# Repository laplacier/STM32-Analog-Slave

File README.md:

https://www.laplacier.com/stm32-analog-slave

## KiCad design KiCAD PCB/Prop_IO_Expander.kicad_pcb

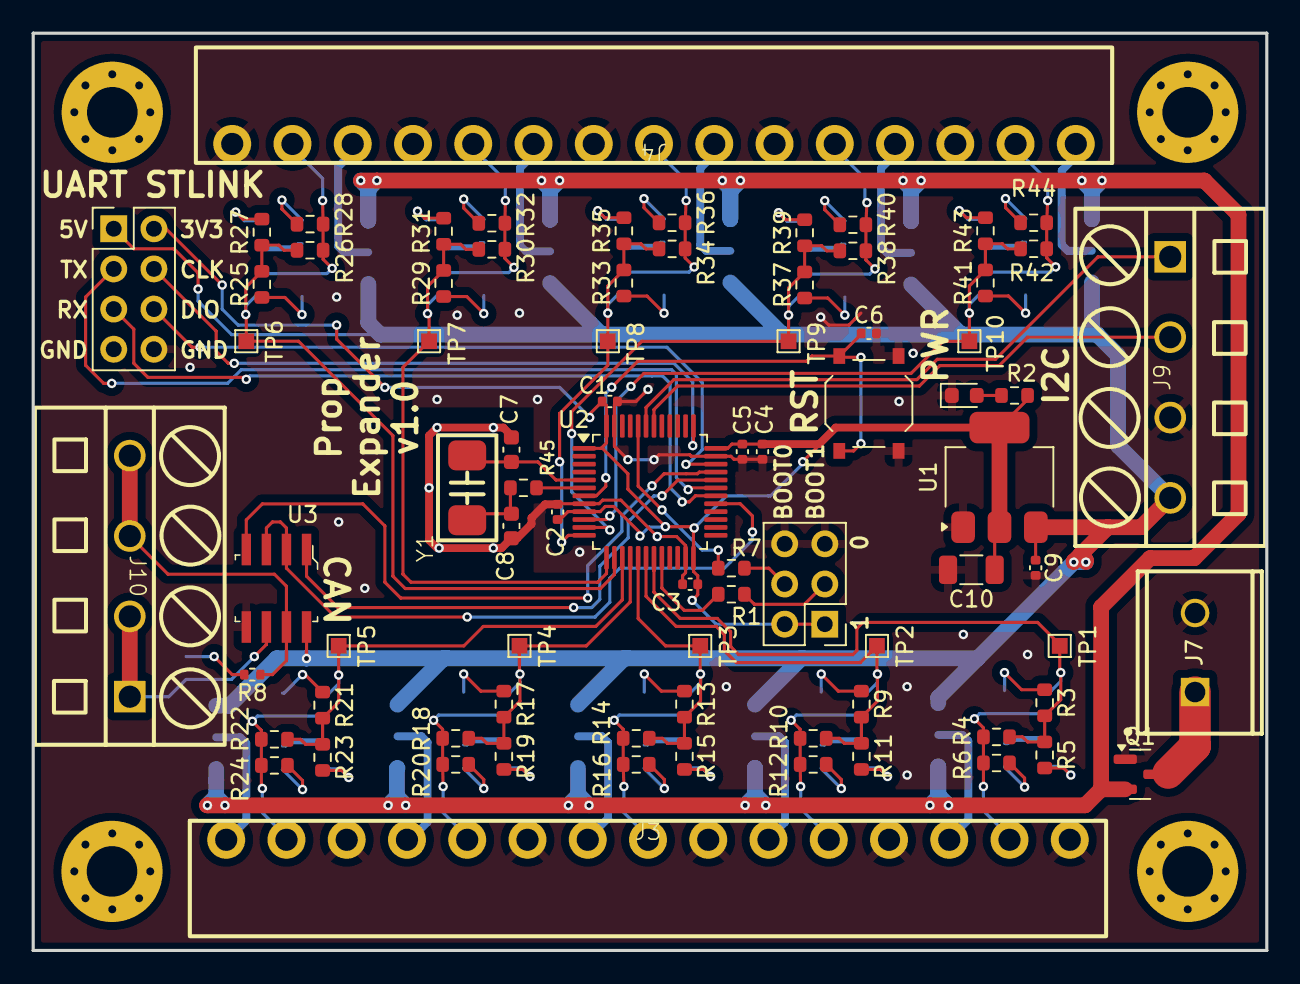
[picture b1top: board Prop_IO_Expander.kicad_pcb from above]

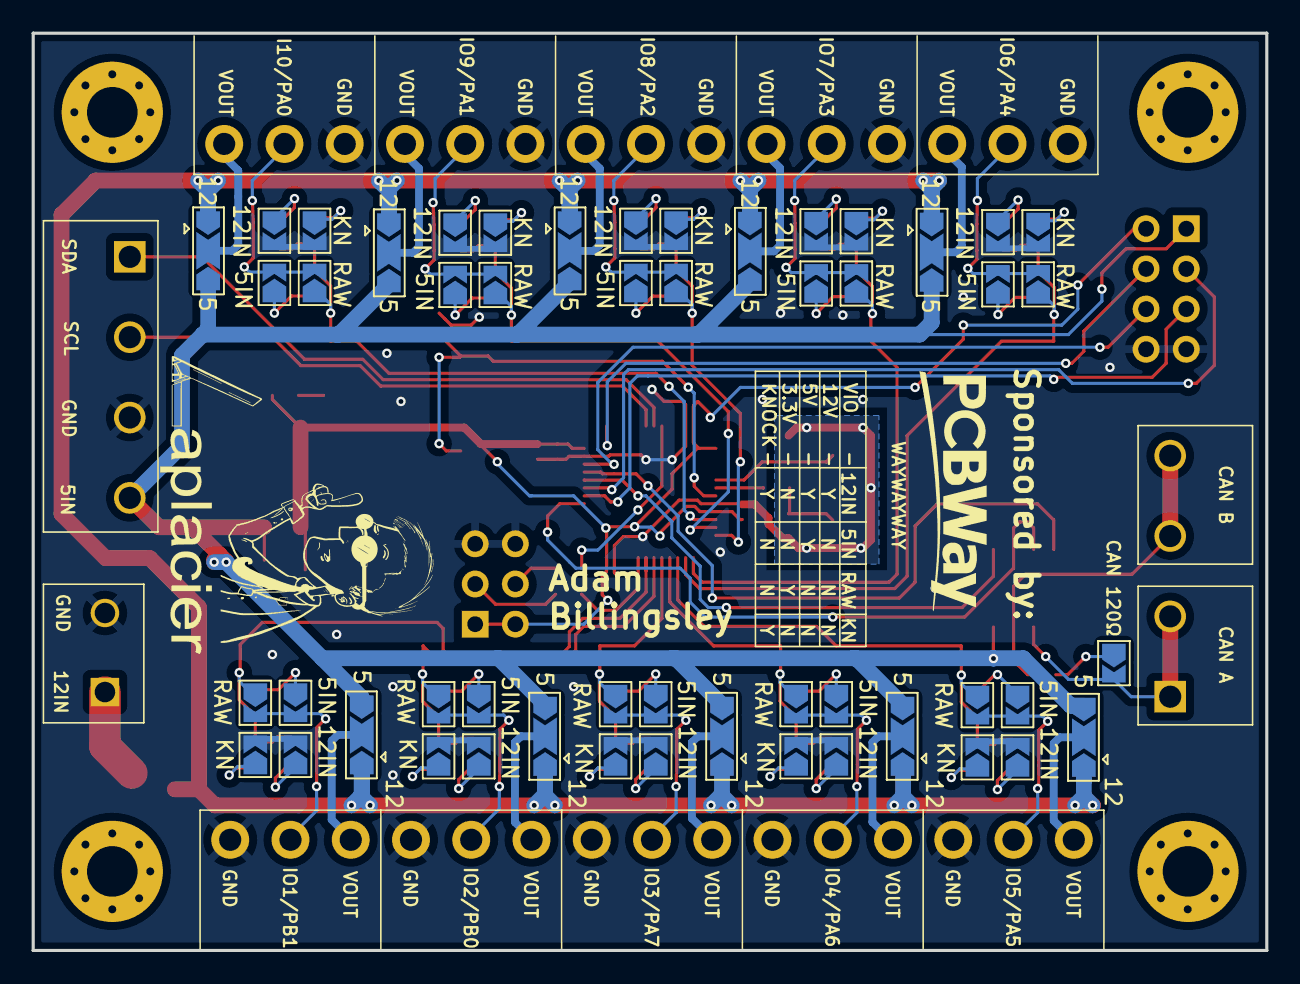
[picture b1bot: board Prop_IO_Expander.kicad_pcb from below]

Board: 2 copper layers, 78.0 x 58.0 mm, 130 parts (51 on the bottom side), 86 nets.

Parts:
C1, C2, C3, C4, C9: 1uF; C_0402_1005Metric
C5, C6: 10nF; C_0402_1005Metric
C7, C8: 30pF; C_0603_1608Metric
C10: 22uF; C_1206_3216Metric
D1: LED; LED_0603_1608Metric
J2: BOOT; PinHeader_2x03_P2.54mm_Vertical
J3, J4: Conn_01x15_Socket; MAX_MX15EDGRC_15P_P3.81_Horizontal
J7: XY301V-A-5.0-2P; TerminalBlock_Wuerth_691137710002_P5.0mm
J8: Conn_02x05_Odd_Even; PinHeader_2x04_P2.54mm_Vertical
J9, J10: Screw_Terminal_01x04; TerminalBlock_Dorabo-4_P5.08mm
JP1, JP6, JP11, JP16, JP21, JP26, JP31, JP36, JP41, JP46: Jumper_3_Open; SolderJumper-3_P2.0mm_Open_TrianglePad1.0x1.5mm
JP2, JP3, JP4, JP5, JP7, JP8, JP9, JP10, JP12, JP13, JP14, JP15, JP17, JP18, JP19, JP20, JP22, JP23, JP24, JP25, JP27, JP28, JP29, JP30, JP32, JP33, JP34, JP35, JP37, JP38, JP39, JP40, JP42, JP43, JP44, JP45, JP47, JP48, JP49, JP50, JP51: Jumper_2_Open; SolderJumper-2_P1.3mm_Open_TrianglePad1.0x1.5mm
Q1: AO3401A; SOT-23
R1, R2, R7: 10k; R_0603_1608Metric
R3, R9, R13, R17, R21, R25, R29, R33, R37, R41: 6.8kΩ; R_0603_1608Metric
R4, R10, R14, R18, R22, R26, R30, R34, R38, R42: 27kΩ; R_0603_1608Metric
R5, R11, R15, R19, R23, R27, R31, R35, R39, R43: 10kΩ; R_0603_1608Metric
R6, R12, R16, R20, R24, R28, R32, R36, R40, R44: 1MΩ; R_0603_1608Metric
R8: 120Ω; R_0402_1005Metric
R45: 680Ω; R_0603_1608Metric
SW1: RESET; SW_Push_1P1T_XKB_TS-1187A
TP1, TP2, TP3, TP4, TP5, TP6, TP7, TP8, TP9, TP10: TestPoint; TestPoint_Pad_1.0x1.0mm
U1: AMS1117-3.3; SOT-223-3_TabPin2
U2: STM32F103C8T6; LQFP-48_7x7mm_P0.5mm
U3: SP3485EN-L_TR; SOIC-8_W3.9mm
Y1: 8MHz; CRYSTAL-SMD_L5.0-W3.2

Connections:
+3.3V: C1.1, C2.1, C3.1, C4.1, C5.1, C10.1, J2.1, J2.2, J8.2, R2.1, U1.2 (VO), U2.1 (VBAT), U2.9 (VDDA), U2.24 (VDD), U2.36 (VDD), U2.48 (VDD)
+5V: C9.1, J8.1, J9.4, JP1.3 (B), JP6.3 (B), JP11.3 (B), JP16.3 (B), JP21.3 (B), JP26.3 (B), JP31.3 (B), JP36.3 (B), JP41.3 (B), JP46.3 (B), U1.3 (VI), U3.8 (VCC)
+12V: JP1.1 (A), JP6.1 (A), JP11.1 (A), JP16.1 (A), JP21.1 (A), JP26.1 (A), JP31.1 (A), JP36.1 (A), JP41.1 (A), JP46.1 (A), Q1.2 (S)
/BOOT0: R7.2, U2.44 (BOOT0)
/BOOT1: R1.1, U2.20 (PB2)
/CAN_EN: U2.29 (PA8), U3.2 (~RE), U3.3 (DE)
/CAN_RX: U2.32 (PA11), U3.1 (RO)
/CAN_TX: U2.33 (PA12), U3.4 (DI)
/I2C_SCL: J9.2, U2.42 (PB6)
/I2C_SDA: J9.1, U2.43 (PB7)
/Input1/INPUT: J3.2, JP2.2 (B), JP3.2 (B), R4.2, R6.1
/Input1/VCC: J3.3, JP1.2 (C)
/Input2/INPUT: J3.5, JP7.2 (B), JP8.2 (B), R10.2, R12.1
/Input2/VCC: J3.6, JP6.2 (C)
/Input3/INPUT: J3.8, JP12.2 (B), JP13.2 (B), R14.2, R16.1
/Input3/VCC: J3.9, JP11.2 (C)
/Input4/INPUT: J3.11, JP17.2 (B), JP18.2 (B), R18.2, R20.1
/Input4/VCC: J3.12, JP16.2 (C)
/Input5/INPUT: J3.14, JP22.2 (B), JP23.2 (B), R22.2, R24.1
/Input5/VCC: J3.15, JP21.2 (C)
/Input6/INPUT: J4.2, JP27.2 (B), JP28.2 (B), R26.2, R28.1
/Input6/VCC: J4.3, JP26.2 (C)
/Input7/INPUT: J4.5, JP32.2 (B), JP33.2 (B), R30.2, R32.1
/Input7/VCC: J4.6, JP31.2 (C)
/Input8/INPUT: J4.8, JP37.2 (B), JP38.2 (B), R34.2, R36.1
/Input8/VCC: J4.9, JP36.2 (C)
/Input9/INPUT: J4.11, JP42.2 (B), JP43.2 (B), R38.2, R40.1
/Input9/VCC: J4.12, JP41.2 (C)
/Input10/INPUT: J4.14, JP47.2 (B), JP48.2 (B), R42.2, R44.1
/Input10/VCC: J4.15, JP46.2 (C)
/NRST: C6.1, SW1.1, U2.7 (NRST)
/PA0: JP48.1 (A), R41.1, R42.1, R43.1, TP10.1, U2.10 (PA0)
/PA1: JP43.1 (A), R37.1, R38.1, R39.1, TP9.1, U2.11 (PA1)
/PA2: JP38.1 (A), R33.1, R34.1, R35.1, TP8.1, U2.12 (PA2)
/PA3: JP33.1 (A), R29.1, R30.1, R31.1, TP7.1, U2.13 (PA3)
/PA4: JP28.1 (A), R25.1, R26.1, R27.1, TP6.1, U2.14 (PA4)
/PA5: JP23.1 (A), R21.1, R22.1, R23.1, TP5.1, U2.15 (PA5)
/PA6: JP18.1 (A), R17.1, R18.1, R19.1, TP4.1, U2.16 (PA6)
/PA7: JP13.1 (A), R13.1, R14.1, R15.1, TP3.1, U2.17 (PA7)
/PB0: JP8.1 (A), R9.1, R10.1, R11.1, TP2.1, U2.18 (PB0)
/PB1: JP3.1 (A), R3.1, R4.1, R5.1, TP1.1, U2.19 (PB1)
/PD0: C7.2, U2.5 (PD0), Y1.2
/PD1: R45.1, U2.6 (PD1)
/SWCLK: J8.4, U2.37 (PA14)
/SWDIO: J8.6, U2.34 (PA13)
/UART_RX0: J8.5, U2.30 (PA9)
/UART_TX0: J8.3, U2.31 (PA10)
GND: C1.2, C2.2, C3.2, C4.2, C5.2, C6.2, C7.1, C8.1, C9.2, C10.2, D1.1 (K), J2.5, J2.6, J3.1, J3.4, J3.7, J3.10, J3.13, J4.1, J4.4, J4.7, J4.10, J4.13, J7.2, J8.7, J8.8, J9.3, JP4.2 (B), JP5.2 (B), JP9.2 (B), JP10.2 (B), JP14.2 (B), JP15.2 (B), JP19.2 (B), JP20.2 (B), JP24.2 (B), JP25.2 (B), JP29.2 (B), JP30.2 (B), JP34.2 (B), JP35.2 (B), JP39.2 (B), JP40.2 (B), JP44.2 (B), JP45.2 (B), JP49.2 (B), JP50.2 (B), Q1.1 (G), SW1.2, U1.1 (GND), U2.8 (VSSA), U2.23 (VSS), U2.35 (VSS), U2.47 (VSS), U3.5 (GND)
unnamed: C8.2, R45.2, Y1.1
unnamed: D1.2 (A), R2.2
unnamed: J2.3, R1.2
unnamed: J2.4, R7.1
unnamed: J10.1, J10.2, JP51.2 (B), U3.6 (A)
unnamed: J10.3, J10.4, R8.2, U3.7 (B)
unnamed: JP2.1 (A), R3.2
unnamed: JP4.1 (A), R6.2
unnamed: JP5.1 (A), R5.2
unnamed: JP7.1 (A), R9.2
unnamed: JP9.1 (A), R12.2
unnamed: JP10.1 (A), R11.2
unnamed: JP12.1 (A), R13.2
unnamed: JP14.1 (A), R16.2
unnamed: JP15.1 (A), R15.2
unnamed: JP17.1 (A), R17.2
unnamed: JP19.1 (A), R20.2
unnamed: JP20.1 (A), R19.2
unnamed: JP22.1 (A), R21.2
unnamed: JP24.1 (A), R24.2
unnamed: JP25.1 (A), R23.2
unnamed: JP27.1 (A), R25.2
unnamed: JP29.1 (A), R28.2
unnamed: JP30.1 (A), R27.2
unnamed: JP32.1 (A), R29.2
unnamed: JP34.1 (A), R32.2
unnamed: JP35.1 (A), R31.2
unnamed: JP37.1 (A), R33.2
unnamed: JP39.1 (A), R36.2
unnamed: JP40.1 (A), R35.2
unnamed: JP42.1 (A), R37.2
unnamed: JP44.1 (A), R40.2
unnamed: JP45.1 (A), R39.2
unnamed: JP47.1 (A), R41.2
unnamed: JP49.1 (A), R44.2
unnamed: JP50.1 (A), R43.2
unnamed: JP51.1 (A), R8.1
VDC: J7.1, Q1.3 (D)

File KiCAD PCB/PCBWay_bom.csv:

Item #,*Designator,*Qty,Manufacturer,*Mfg Part #,Description / Value,*Package/Footprint ,Type,Your Instructions / Notes
1,"C1,C2,C3,C4,C9",5,Samsung Electro-Mechanics,CL05A105KA5NQNC ,25V 1uF X5R ±10% 0402 Multilayer Ceramic Capacitors MLCC - SMD/SMT ROHS ,0402,SMD,
2,"C5,C6",2,Samsung Electro-Mechanics,CL05B103KB5NNNC ,50V 10nF X7R ±10% 0402 Multilayer Ceramic Capacitors MLCC - SMD/SMT ROHS ,0402,SMD,
3,"C7,C8",2,FH (Guangdong Fenghua Advanced Tech) ,0603CG300J500NT ,50V 30pF C0G ±5% 0603 Multilayer Ceramic Capacitors MLCC - SMD/SMT ROHS ,0603,SMD,
4,C10,1,Samsung Electro-Mechanics,CL31A226KAHNNNE ,25V 22uF X5R ±10% 1206 Multilayer Ceramic Capacitors MLCC - SMD/SMT ROHS ,1206,SMD,
5,D1,1,Hubei KENTO Elec ,KT-0603R ,-40℃~+85℃ Red 0603 Light Emitting Diodes (LED) ROHS ,0603,SMD,
6,J2,1,,,Pin Header_2x03_P2.54mm_Vertical,SMT-2x03P,thru-hole,
7,"J3,J4",2,MAX,MX15EDGRC-3.81-15P-GN01-Cu-A ,"300V 8A 15 Bend -40℃~+105℃ Copper Alloy 1 3.81mm 1x15P Green Board Edge/Receptacle-Close Tin Push-Pull,P=3.81mm Pluggable System Terminal Block ROHS ",SMT-15P,thru-hole,
8,J8,1,,Conn_02x05_Odd_Even,Pin Header_2x04_P2.54mm_Vertical,SMT-2x04P,thru-hole,
9,"J9,J10",2,DORABO,DB127S-5.08-4P-GN ,P=5.08mm Screw terminal ROHS ,SMT-4P,thru-hole,
10,Q1,1,Alpha & Omega Semicon,AO3401A,"30V 4A 44mΩ@10V,4.3A 1.4W 1.3V@250uA 1PCSPChannel SOT-23 MOSFETs ROHS ",23-SOT,SMD,
11,"R1,R2,R7",3,UNI-ROYAL(厚声),0603WAF1002T5E,100mW Thick Film Resistors 75V ±100ppm/℃ ±1% 10kΩ 0603 Chip Resistor - Surface Mount ROHS ,0603,SMD,
12,"R3,R9,R13,R17,R21,R25,R29,R33,R37,R41",10,UNI-ROYAL(厚声),0603WAF6801T5E ,100mW Thick Film Resistors 75V ±100ppm/℃ ±1% 6.8kΩ 0603 Chip Resistor - Surface Mount ROHS ,0603,SMD,
13,"R4,R10,R14,R18,R22,R26,R30,R34,R38,R42",10,UNI-ROYAL(厚声),0603WAF2702T5E ,100mW Thick Film Resistors 75V ±100ppm/℃ ±1% 27kΩ 0603 Chip Resistor - Surface Mount ROHS ,0603,SMD,
14,"R5,R11,R15,R19,R23,R27,R31,R35,R39,R43",10,UNI-ROYAL(厚声),0603WAF1002T5E ,100mW Thick Film Resistors 75V ±100ppm/℃ ±1% 10kΩ 0603 Chip Resistor - Surface Mount ROHS ,0603,SMD,
15,"R6,R12,R16,R20,R24,R28,R32,R36,R40,R44",10,UNI-ROYAL(厚声),0603WAF1004T5E ,100mW Thick Film Resistors 75V ±100ppm/℃ ±1% 1MΩ 0603 Chip Resistor - Surface Mount ROHS ,0603,SMD,
16,R8,1,UNI-ROYAL(厚声),0402WGF1200TCE ,62.5mW Thick Film Resistors 50V ±100ppm/℃ ±1% 120Ω 0402 Chip Resistor - Surface Mount ROHS ,0402,SMD,
17,R45,1,UNI-ROYAL(厚声),0603WAF6800T5E ,100mW Thick Film Resistors 75V ±100ppm/℃ ±1% 680Ω 0603 Chip Resistor - Surface Mount ROHS ,0603,SMD,
18,SW1,1,XKB Connection ,TS-1187A-B-A-B ,"No Without 50mA 5.1mm 100,000 Times 160gf 12V 5.1mm 1.5mm Round Button Brick nogging SPST SMD Tactile Switches ROHS",SMD,SMD,
19,U1,1,Advanced Monolithic Systems ,AMS1117-3.3,72dB@(120Hz) 1A Fixed 3.3V Positive electrode SOT-223-3 Linear Voltage Regulators (LDO) ROHS ,223-3-SOT,SMD,
20,U2,1,STMicroelectronics,STM32F103C8T6,64KB 2V~3.6V ARM-M3 20KB 72MHz FLASH 37 LQFP-48(7x7) Microcontroller Units (MCUs/MPUs/SOCs) ROHS ,48-LQFP,SMD/LQFP,
21,U3,1,"MaxLinear, Inc.",SP3485EN-L_TR,transceiver 10Mbps 1/1 SOIC-8 RS-485/RS-422 ICs ROHS ,8-SOIC,SMD,
22,Y1,1,YXC ,X50328MSB2GI ,8MHz Surface mount crystal oscillator 20pF ±10ppm ±20ppm SMD5032 Crystals ROHS ,SMD,SMD,

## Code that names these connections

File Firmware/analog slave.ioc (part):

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Mcu.Name=STM32F030C8Tx
Mcu.Package=LQFP48
Mcu.UserName=STM32F030C8Tx
PA0.Mode=IN0
PA0.Signal=ADC_IN0
PA1.Mode=IN1
PA1.Signal=ADC_IN1
PA2.Mode=IN2
PA2.Signal=ADC_IN2
PA3.Mode=IN3
PA3.Signal=ADC_IN3
PA4.Mode=IN4
PA4.Signal=ADC_IN4
PA5.Mode=IN5
PA5.Signal=ADC_IN5
PA6.Mode=IN6
PA6.Signal=ADC_IN6
PA7.Mode=IN7
PA7.Signal=ADC_IN7
PB0.Mode=IN8
PB0.Signal=ADC_IN8
PB1.Mode=IN9
PB1.Signal=ADC_IN9
PB6.Mode=I2C
PB6.Signal=I2C1_SCL
PB7.Mode=I2C
PB7.Signal=I2C1_SDA
board=custom

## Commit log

2024-08-11 Upload files
